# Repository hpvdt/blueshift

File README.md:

# Blueshift

Repository for our what would have been our 2020 ASME entry, Blueshift. Although the vehicle was never completed, the electronics were. The system is heavily based off of TITAN given they are both depend on a video system for the riders which is overlaid with vehicle data.

## Changes from TITAN

 However it has some changes from TITAN:
- Lighting hardware (and control) to meet road legality requirements
- Hardware was designed as an RPi HAT for a more compact system.
- Telemetry was operated by the microcontroller, not the RPi as on TITAN.
- Moved from a Python based overlay system to C based one to improve overlay update rate and prevent the overlay blacking out the video on occasion.

All systems were tested from home during the first set of lockdowns during COVID and were successful. So it is likely they would have worked just as well had the bike been built.

## Outcome

Work on this project ceased once the C-based overlay was working and telemetry was worked into it. Much of what was done for Blueshift will now go into improving TITAN for the future.

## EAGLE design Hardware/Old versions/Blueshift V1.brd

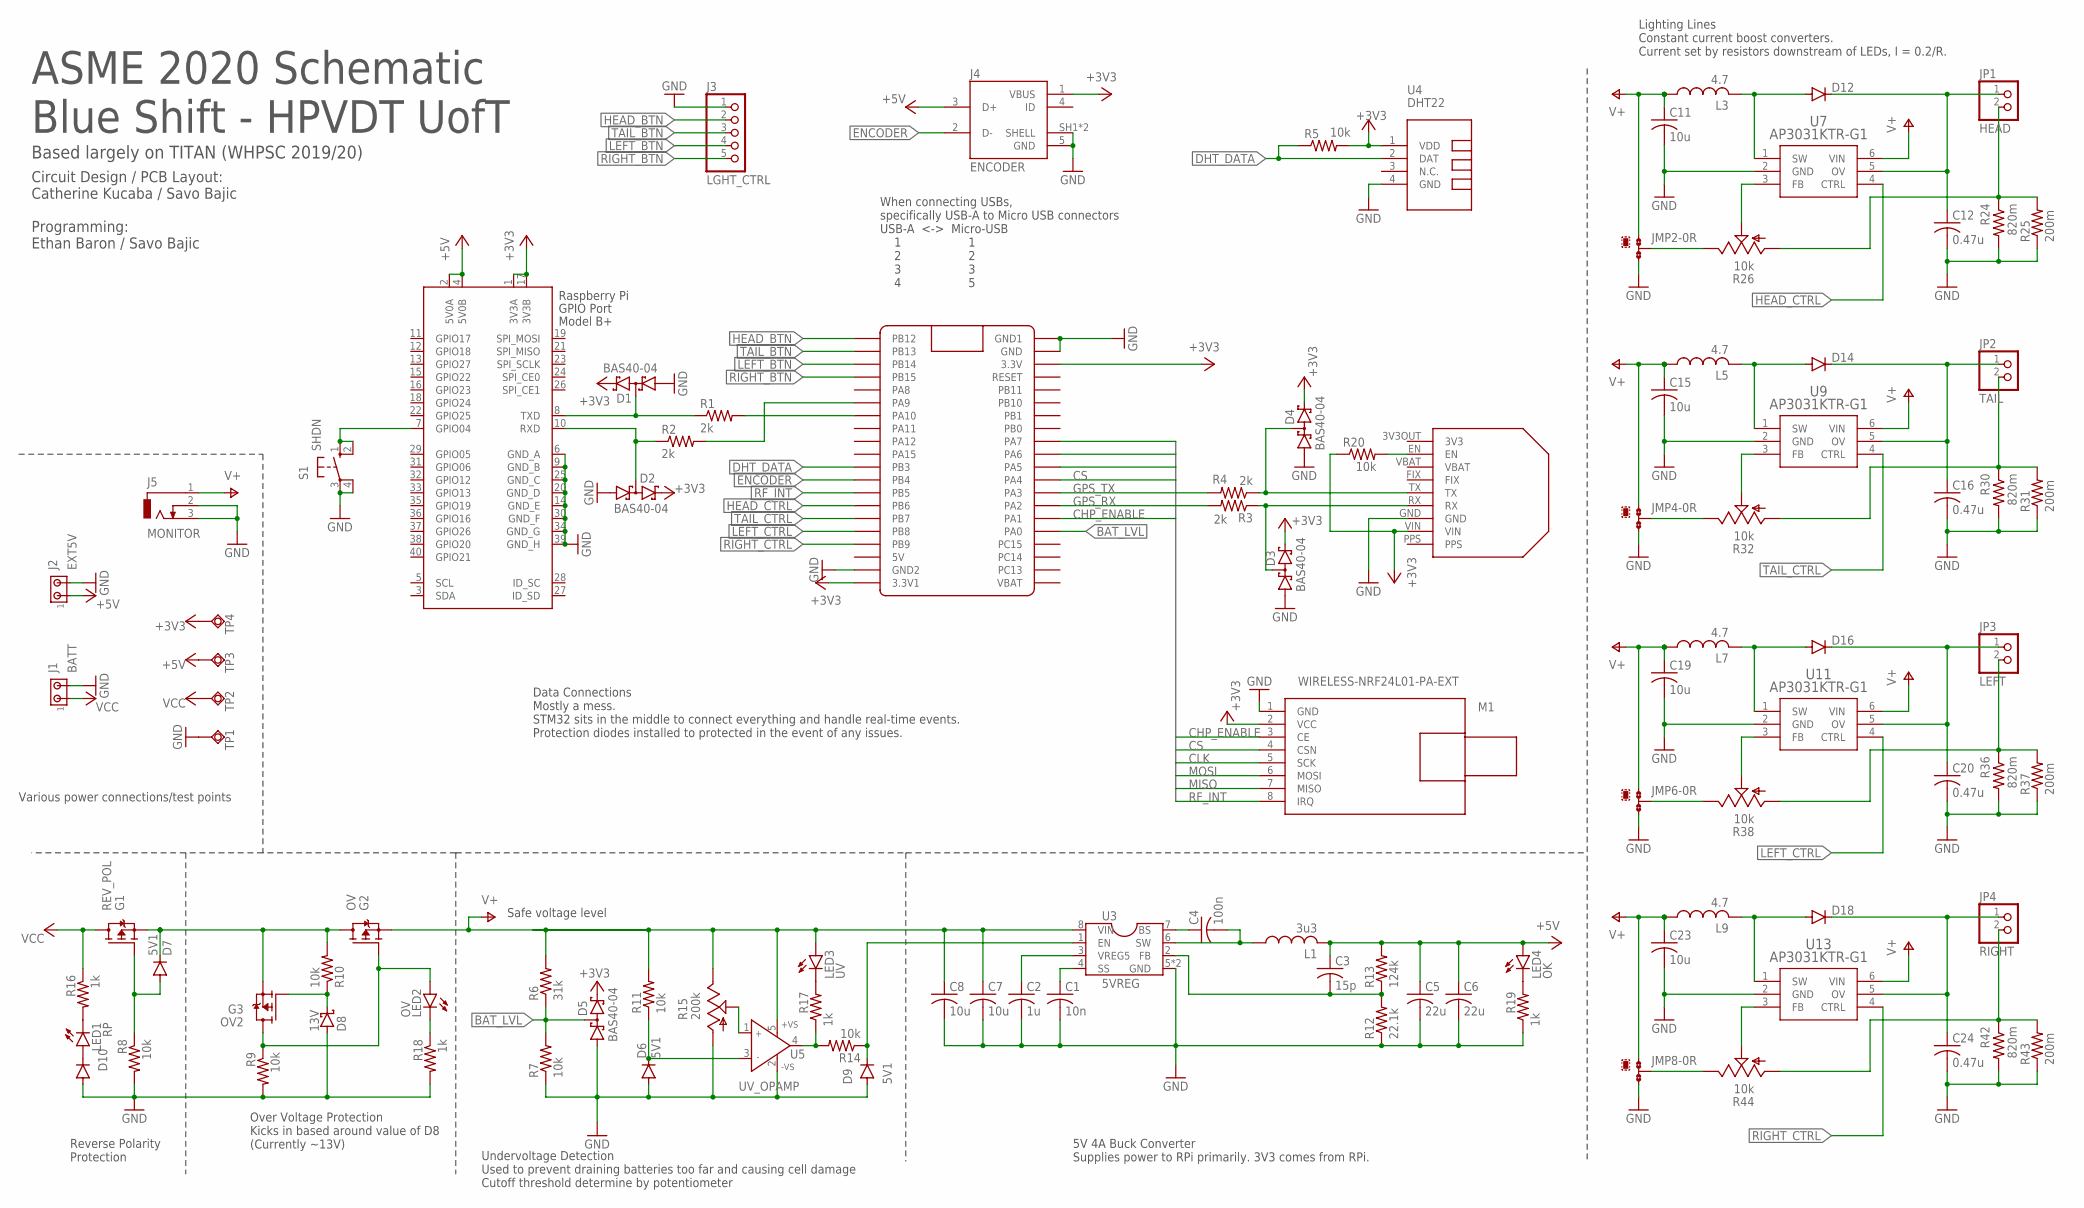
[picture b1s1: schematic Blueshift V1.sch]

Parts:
C1: 10n; C0402
C2: 1u; C0402
C3: 15p; C0402
C4: 100n; C0402
C5, C6: 22u; C0805
C7, C8: 10u; C0805
C11, C15, C19, C23: 10u; C1206K
C12, C16, C20, C24: 0.47u; C1206K
D1, D2, D3, D4, D5: BAS40-04; SOT23
D6, D7, D9: 5V1; SOD323-R
D8: 13V; SOT23
D10: DIODE-SOD80C; SOD80C
D12, D14, D16, D18: DIODE-DO-214AC; DO-214AC
G1: REV_POL; TSOP-6
G2: OV; TSOP-6
G3: OV2; TSOP-6
J1: BATT; 1X2MTA
J2: EXT5V; 1X2MTA
J3: LGHT_CTRL; 1X05
J4: ENCODER; TE_2172034-1
J5: MONITOR; DCJ0303
JMP2, JMP4, JMP6, JMP8: 0R-JUMPA; A0R-JMP
JP1: HEAD; 1X02
JP2: TAIL; 1X02
JP3: LEFT; 1X02
JP4: RIGHT; 1X02
L1: 3u3; SDES064T
L3, L5, L7, L9: 4.7; INDDFN600X600X280-2N
LED1: RP; SML0805
LED2: OV; SML0805
LED3: UV; SML0805
LED4: OK; SML0805
M1: WIRELESS-NRF24L01-PA-EXT
M2: ULTIMATE-GPS; ULTIMATE_GPS
R1, R2, R3, R4: 2k; R0402
R5, R7, R8, R9, R10, R11, R14, R20: 10k; R0402
R6: 31k; R0402
R12: 22.1k; R0402
R13: 124k; R0402
R15: 200k; CA6V
R16, R17, R18, R19: 1k; R0402
R24, R30, R36, R42: 820m; R0603
R25, R31, R37, R43: 200m; R0805
R26, R32, R38, R44: 10k; RJ9W
S1: SHDN; B3F-10XX
TP1: TPSQTP20SQ; TP20SQ
TP2, TP3, TP4: TPSQTP20R; TP20R
U1: RASPI_HAT; RASPI_BOARD_B+HAT_CF
U2: BLUEPILL; BLUE_PILL
U3: 5VREG; SO-8EP
U4: DHT22; TEMP-HUM-SENSOR-DHT22
U5: UV_OPAMP; SOT-753
U7, U9, U11, U13: AP3031KTR-G1; SOT23-6

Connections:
5V_FB: C3.2, R12.2, R13.1, U3.2 (FB)
+3V3: D1.2 (C2), D2.2 (C2), D3.2 (C2), D4.2 (C2), D5.2 (C2), J4.1 (VBUS), M1.2 (VCC), M2.VIN, R5.2, R20.1, TP4.TP, U1.1 (3V3A), U1.17 (3V3B), U2.P$20 (3.3V1), U2.P$23 (3.3V), U4.1 (VDD)
+5V: C3.1, C5.1, C6.1, J2.1, J4.3 (D+), L1.2, LED4.A, R13.2, TP3.TP, U1.2 (5V0A), U1.4 (5V0B)
BAT_LVL: D5.3 (C1A2), R6.1, R7.2, U2.P$36 (PA0)
CHP_ENABLE: M1.3 (CE), U2.P$35 (PA1)
CLK: M1.5 (SCK), U2.P$31 (PA5)
CS: M1.4 (CSN), U2.P$32 (PA4)
DHT_DATA: R5.1, U2.P$11 (PB3), U4.2 (DAT)
ENCODER: J4.2 (D-), U2.P$12 (PB4)
GND: C1.2, C2.2, C5.2, C6.2, C7.2, C8.2, C11.2, C12.2, C15.2, C16.2, C19.2, C20.2, C23.2, C24.2, D1.1 (A1), D2.1 (A1), D3.1 (A1), D4.1 (A1), D5.1 (A1), D6.A, D8.1 (A), D9.A, D10.A, J1.2, J2.2, J3.1, J4.5 (GND), J4.SH1 (SHELL), J4.SH2 (SHELL), J5.2, J5.3, JMP2.3, JMP4.3, JMP6.3, JMP8.3, M1.1 (GND), M2.GND, R7.1, R8.2, R9.2, R12.1, R15.A, R18.2, R19.1, R24.2, R25.1, R30.2, R31.1, R36.2, R37.1, R42.2, R43.1, S1.3, S1.4 (P1), TP1.TP, U1.6 (GND_A), U1.9 (GND_B), U1.14 (GND_E), U1.20 (GND_D), U1.25 (GND_C), U1.30 (GND_F), U1.34 (GND_G), U1.39 (GND_H), U2.P$19 (GND2), U2.P$21 (GND1), U2.P$22 (GND), U3.5 (GND), U3.TP (GND), U4.4 (GND), U5.2 (-VS), U7.2 (GND), U9.2 (GND), U11.2 (GND), U13.2 (GND)
GPS_RX: R3.2, U2.P$34 (PA2)
GPS_TX: R4.2, U2.P$33 (PA3)
HEAD_BTN: J3.2, U2.P$1 (PB12)
HEAD_CTRL: U2.P$14 (PB6), U7.4 (CTRL)
LEFT_BTN: J3.4, U2.P$3 (PB14)
LEFT_CTRL: U2.P$16 (PB8), U11.4 (CTRL)
MISO: M1.7 (MISO), U2.P$30 (PA6)
MOSI: M1.6 (MOSI), U2.P$29 (PA7)
unnamed: R1.2, U2.P$7 (PA10)
unnamed: R2.2, U2.P$6 (PA9)
unnamed: D1.3 (C1A2), R1.1, U1.8 (TXD)
unnamed: D2.3 (C1A2), R2.1, U1.10 (RXD)
unnamed: D3.3 (C1A2), M2.RX, R3.1
unnamed: S1.1 (S), S1.2 (S1), U1.7 (GPIO04)
unnamed: D8.3 (C), G3.3 (G), R10.1
unnamed: D7.A, G1.3 (G), R8.1
unnamed: D4.3 (C1A2), M2.TX, R4.1
unnamed: G2.3 (G), G3.1 (D), G3.2 (D), G3.5 (D), G3.6 (D), LED2.A, R9.1
unnamed: LED3.C, R17.2
unnamed: C1.1, U3.4 (SS)
unnamed: D6.C, R11.1, U5.3 (IN-)
unnamed: C4.2, L1.1, U3.6 (SW)
unnamed: C2.1, U3.3 (VREG5)
unnamed: C4.1, U3.7 (BS)
unnamed: R14.2, R17.1, U5.4 (OUT)
unnamed: D9.C, R14.1, U3.1 (EN)
unnamed: R15.S, U5.1 (IN+)
unnamed: LED1.C, R16.2
unnamed: D10.C, LED1.A
unnamed: M2.EN, R20.2
unnamed: LED2.C, R18.1
unnamed: LED4.C, R19.2
unnamed: D7.C, G1.4 (S), G2.1 (D), G2.2 (D), G2.5 (D), G2.6 (D), G3.4 (S), R10.2
unnamed: D12.A, L3.2, U7.1 (SW)
unnamed: JMP2.2, R26.E
unnamed: R26.S, U7.3 (FB)
unnamed: C12.1, D12.C, JP1.1, U7.5 (OV)
unnamed: JP1.2, R24.1, R25.2, R26.A
unnamed: D14.A, L5.2, U9.1 (SW)
unnamed: JMP4.2, R32.E
unnamed: R32.S, U9.3 (FB)
unnamed: C16.1, D14.C, JP2.1, U9.5 (OV)
unnamed: JP2.2, R30.1, R31.2, R32.A
unnamed: D16.A, L7.2, U11.1 (SW)
unnamed: JMP6.2, R38.E
unnamed: R38.S, U11.3 (FB)
unnamed: C20.1, D16.C, JP3.1, U11.5 (OV)
unnamed: JP3.2, R36.1, R37.2, R38.A
unnamed: D18.A, L9.2, U13.1 (SW)
unnamed: JMP8.2, R44.E
unnamed: R44.S, U13.3 (FB)
unnamed: C24.1, D18.C, JP4.1, U13.5 (OV)
unnamed: JP4.2, R42.1, R43.2, R44.A
RF_INT: M1.8 (IRQ), U2.P$13 (PB5)
RIGHT_BTN: J3.5, U2.P$4 (PB15)
RIGHT_CTRL: U2.P$17 (PB9), U13.4 (CTRL)
TAIL_BTN: J3.3, U2.P$2 (PB13)
TAIL_CTRL: U2.P$15 (PB7), U9.4 (CTRL)
V+: C7.1, C8.1, C11.1, C15.1, C19.1, C23.1, G2.4 (S), J5.1, JMP2.1, JMP4.1, JMP6.1, JMP8.1, L3.1, L5.1, L7.1, L9.1, LED3.A, R6.2, R11.2, R15.E, U3.8 (VIN), U5.5 (+VS), U7.6 (VIN), U9.6 (VIN), U11.6 (VIN), U13.6 (VIN)
VCC: G1.1 (D), G1.2 (D), G1.5 (D), G1.6 (D), J1.1, R16.1, TP2.TP

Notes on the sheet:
When connecting USBs, specifically USB-A to Micro USB connectors USB-A <-> Micro-USB 1 1 2 2 3 3 4 5
Safe voltage level
Various power connections/test points
Undervoltage Detection Used to prevent draining batteries too far and causing cell damage Cutoff threshold determine by potentiometer
5V 4A Buck Converter Supplies power to RPi primarily. 3V3 comes from RPi.
Lighting Lines Constant current boost converters. Current set by resistors downstream of LEDs, I = 0.2/R.
Data Connections Mostly a mess. STM32 sits in the middle to connect everything and handle real-time events. Protection diodes installed to protected in the event of any issues.
Reverse Polarity Protection
Over Voltage Protection Kicks in based around value of D8 (Currently ~13V)
ASME 2020 Schematic Blue Shift - HPVDT UofT
Based largely on TITAN (WHPSC 2019/20)
Circuit Design / PCB Layout: Catherine Kucaba / Savo Bajic Programming: Ethan Baron / Savo Bajic

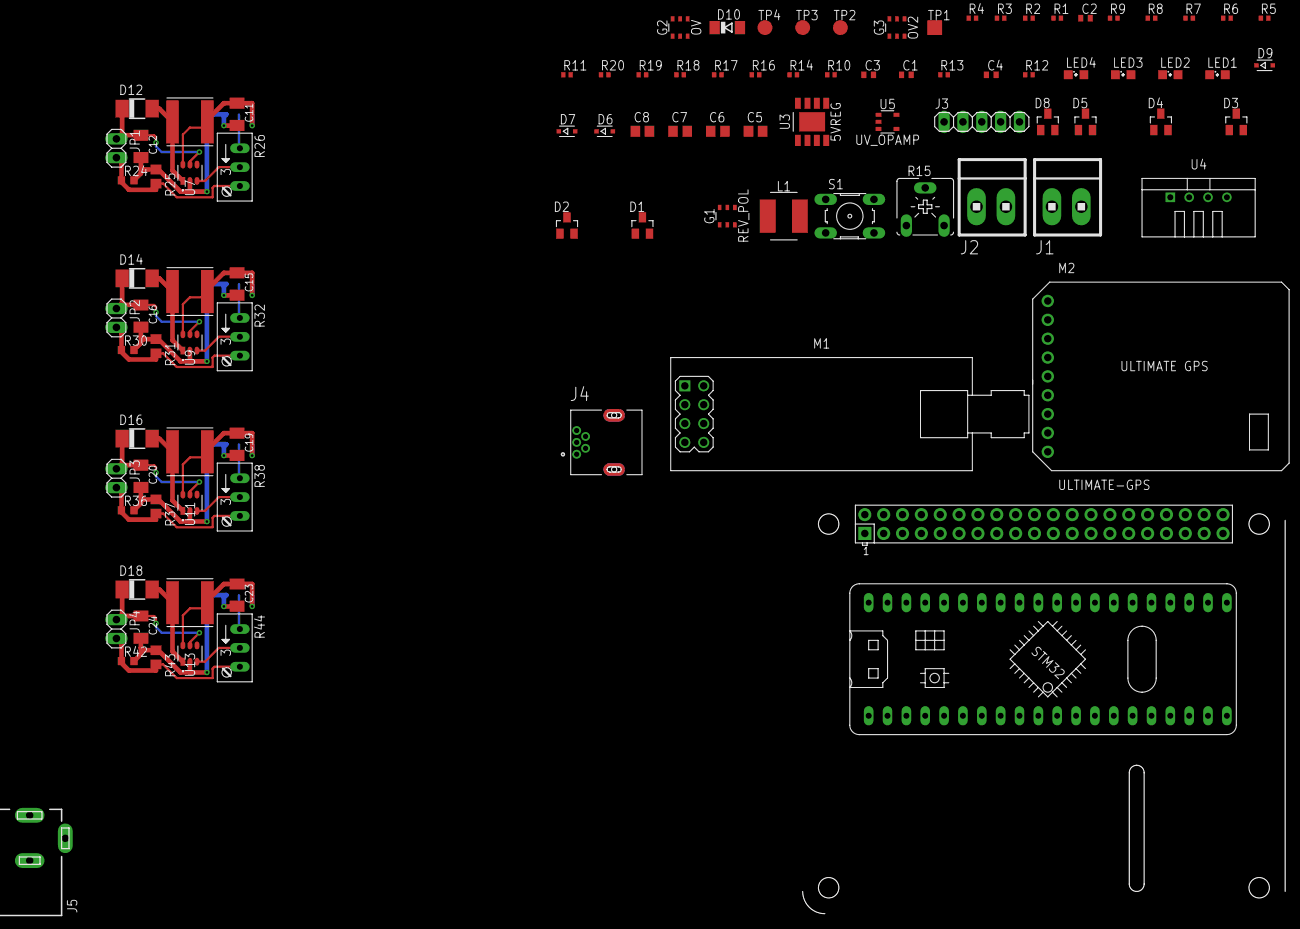
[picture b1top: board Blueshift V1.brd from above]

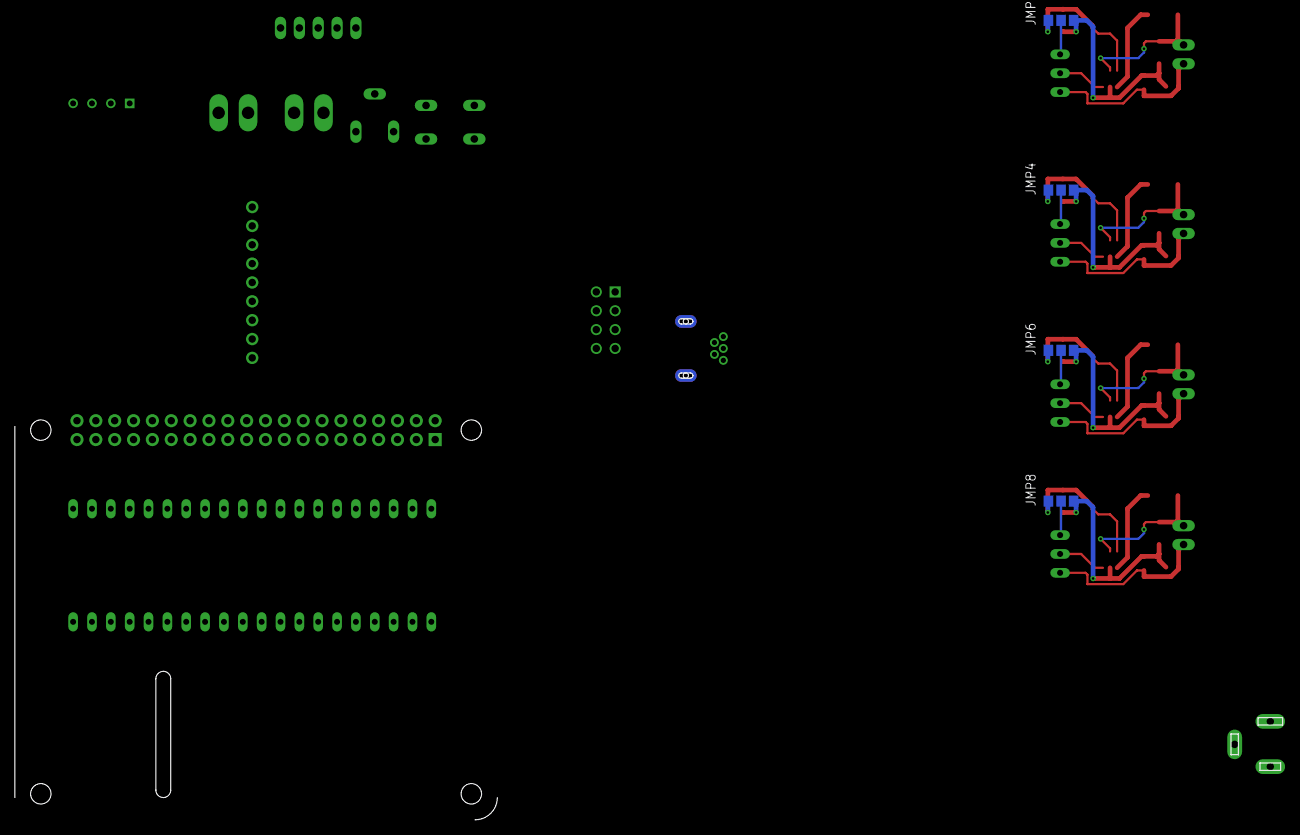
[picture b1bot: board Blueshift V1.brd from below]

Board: 2 copper layers, 103 parts (4 on the bottom side), 70 nets.

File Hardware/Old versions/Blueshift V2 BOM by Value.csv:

"Qty";"Value";"Device";"Package";"Parts";"Description";"";
"4";"";"DIODE-DO-214AC";"DO-214AC";"D12, D14, D16, D18";"DIODE";"";
"1";"";"DIODE-SOD80C";"SOD80C";"D10";"DIODE";"";
"4";"0.47u";"C-USC1206K";"C1206K";"C12, C16, C20, C24";"CAPACITOR, American symbol";"";
"4";"0R-JUMPA";"0R-JUMPA";"A0R-JMP";"JMP2, JMP4, JMP6, JMP8";"SMD 0R 0805 Jumper";"";
"1";"100n";"C-USC0402";"C0402";"C4";"CAPACITOR, American symbol";"";
"12";"10k";"R-US_R0402";"R0402";"R5, R7, R8, R9, R10, R11, R14, R20, R21, R22, R23, R27";"RESISTOR, American symbol";"";
"5";"10k";"TRIM_US-RJ9W";"RJ9W";"R26, R28, R32, R38, R44";"POTENTIOMETER";"";
"1";"10n";"C-USC0402";"C0402";"C1";"CAPACITOR, American symbol";"";
"2";"10u";"C-USC0805";"C0805";"C7, C8";"CAPACITOR, American symbol";"";
"4";"10u";"C-USC1206K";"C1206K";"C11, C15, C19, C23";"CAPACITOR, American symbol";"";
"1";"124k";"R-US_R0402";"R0402";"R13";"RESISTOR, American symbol";"";
"1";"13V";"BAS70";"SOT23";"D8";"Silicon Schottky Diodes";"";
"1";"15p";"C-USC0402";"C0402";"C3";"CAPACITOR, American symbol";"";
"4";"1k";"R-US_R0402";"R0402";"R16, R17, R18, R19";"RESISTOR, American symbol";"";
"1";"1u";"C-USC0402";"C0402";"C2";"CAPACITOR, American symbol";"";
"4";"200m";"R-US_R0805";"R0805";"R25, R31, R37, R43";"RESISTOR, American symbol";"";
"1";"22.1k";"R-US_R0402";"R0402";"R12";"RESISTOR, American symbol";"";
"2";"22u";"C-USC0805";"C0805";"C5, C6";"CAPACITOR, American symbol";"";
"4";"2k";"R-US_R0402";"R0402";"R1, R2, R3, R4";"RESISTOR, American symbol";"";
"1";"31k";"R-US_R0402";"R0402";"R6";"RESISTOR, American symbol";"";
"1";"3u3";"SDES064T-3R3MS";"SDES064T";"L1";"";"";
"4";"4u7";"NR6028NR6028";"INDDFN600X600X280-2N";"L3, L5, L7, L9";"";"";
"3";"5V1";"DIODE-SOD323-R";"SOD323-R";"D6, D7, D9";"DIODE";"";
"1";"5VREG";"AP65450SP-13";"SO-8EP";"U3";"AP65450";"";
"4";"820m";"R-US_R0603";"R0603";"R24, R30, R36, R42";"RESISTOR, American symbol";"";
"4";"AP3031KTR-G1";"AP3031KTR-G1";"SOT23-6";"U7, U9, U11, U13";"AP3031 step-up LED driver chip for LEDs up to 1.4A";"";
"5";"BAS40-04";"BAS40-04";"SOT23";"D1, D2, D3, D4, D5";"Silicon Schottky Diodes";"";
"1";"BATT";"MTA02-156";"1X2MTA";"J1";"AMP connector";"";
"1";"BLUEPILL";"BLUE_PILL";"BLUE_PILL";"U2";"";"";
"1";"DHT22";"TEMP-HUM-SENSOR-DHT22";"TEMP-HUM-SENSOR-DHT22";"U4";"DHT22 - digital humidity & temperature sensor";"";
"1";"ENCODER";"2172034-1";"TE_2172034-1";"J4";"CONN RCPT USB MINI B 2.0 PCB R/A";"";
"1";"EXT5V";"MTA02-156";"1X2MTA";"J2";"AMP connector";"";
"1";"HEAD";"PINHD-1X2";"1X02";"JP1";"PIN HEADER";"";
"1";"LEFT";"PINHD-1X2";"1X02";"JP3";"PIN HEADER";"";
"1";"LGHT_CTRL";"PINHD-1X5";"1X05";"J3";"PIN HEADER";"";
"1";"MONITOR";"DCJ0303";"DCJ0303";"J5";"DC POWER JACK";"";
"1";"OK";"LEDSML0805";"SML0805";"LED4";"LED";"";
"1";"OV";"LEDSML0805";"SML0805";"LED2";"LED";"";
"1";"OV";"SI3493DDV-T1-GE3";"TSOP-6";"G2";"20V P-CH MOSFET";"";
"1";"OV2";"SI3493DDV-T1-GE3";"TSOP-6";"G3";"20V P-CH MOSFET";"";
"1";"RASPI_HAT";"RASPI_HAT";"RASPI_BOARD_B+HAT_CF";"U1";"";"";
"1";"REV_POL";"SI3493DDV-T1-GE3";"TSOP-6";"G1";"20V P-CH MOSFET";"";
"1";"RIGHT";"PINHD-1X2";"1X02";"JP4";"PIN HEADER";"";
"1";"RP";"LEDSML0805";"SML0805";"LED1";"LED";"";
"1";"SHDN";"10-XX";"B3F-10XX";"S1";"OMRON SWITCH";"";
"1";"TAIL";"PINHD-1X2";"1X02";"JP2";"PIN HEADER";"";
"3";"TPSQTP20R";"TPSQTP20R";"TP20R";"TP2, TP3, TP4";"Test pad";"";
"1";"TPSQTP20SQ";"TPSQTP20SQ";"TP20SQ";"TP1";"Test pad";"";
"1";"ULTIMATE-GPS";"ULTIMATE-GPS";"ULTIMATE_GPS";"M2";"";"";
"1";"UV";"LEDSML0805";"SML0805";"LED3";"LED";"";
"1";"UV_OPAMP";"TA75S558F,LF";"SOT-753";"U5";"";"";
"1";"WIRELESS-NRF24L01-PA-EXT";"WIRELESS-NRF24L01-PA-EXT";"WIRELESS-NRF24L01-PA-EXT";"M1";"2.4 GHz Wireless Module based on NRF24L01 chip with preamplifier and external antenna";"";

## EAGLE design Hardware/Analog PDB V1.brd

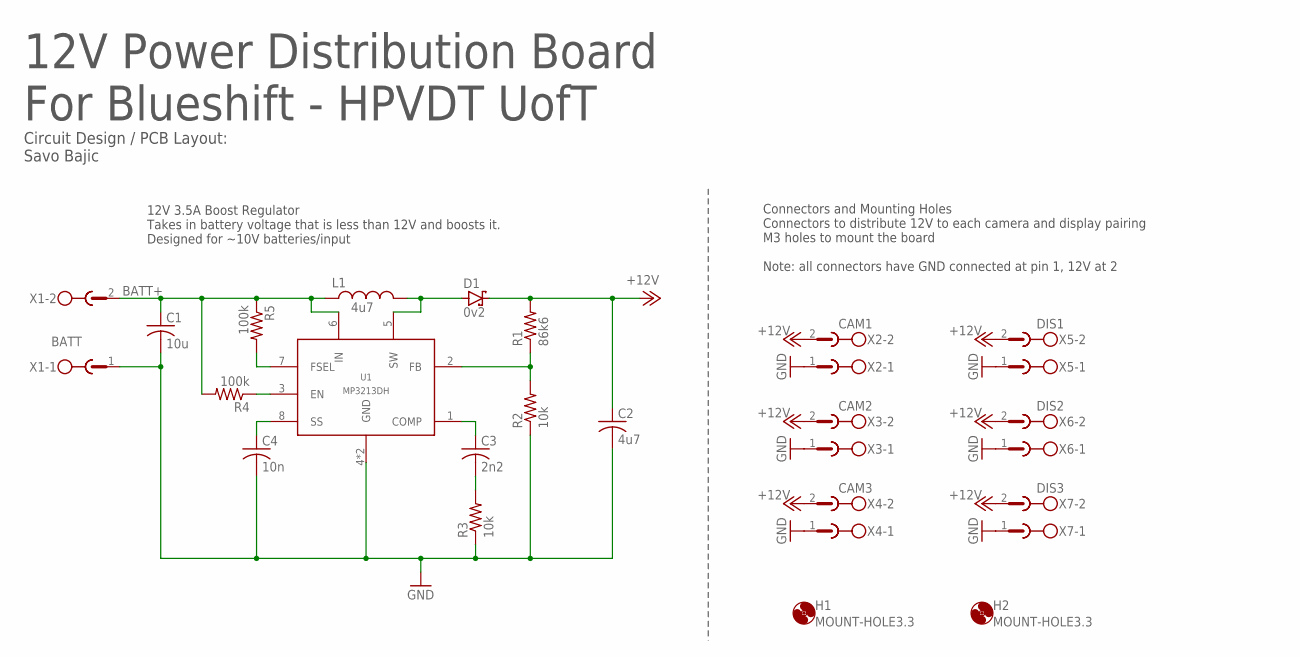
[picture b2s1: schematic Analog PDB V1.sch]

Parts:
C1: 10u; C0603
C2: 4u7; C0603
C3: 2n2; C0603
C4: 10n; C0603
D1: 0v2; DO-214AB
H1, H2: MOUNT-HOLE3.3; 3,3
L1: 4u7; SDES053T
R1: 86k6; R0402
R2, R3: 10k; R0402
R4, R5: 100k; R0402
U1: MP3213DH; 8-TSSOP
X1: BATT; MSTBV2
X2: CAM1; MSTBV2
X3: CAM2; MSTBV2
X4: CAM3; MSTBV2
X5: DIS1; MSTBV2
X6: DIS2; MSTBV2
X7: DIS3; MSTBV2

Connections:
+12V: C2.1, D1.C, R1.2, X2.2, X3.2, X4.2, X5.2, X6.2, X7.2
BATT+: C1.1, L1.1, R4.2, R5.1, U1.6 (IN), X1.2
EN: R4.1, U1.3 (EN)
FEEDBACK: R1.1, R2.2, U1.2 (FB)
FREQSELECT: R5.2, U1.7 (FSEL)
GND: C1.2, C2.2, C4.2, R2.1, R3.1, U1.4 (GND), U1.P (GND), X1.1, X2.1, X3.1, X4.1, X5.1, X6.1, X7.1
unnamed: D1.A, L1.2, U1.5 (SW)
unnamed: C3.1, U1.1 (COMP)
unnamed: C3.2, R3.2
SOFTSTART: C4.1, U1.8 (SS)

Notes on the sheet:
12V 3.5A Boost Regulator Takes in battery voltage that is less than 12V and boosts it. Designed for ~10V batteries/input
Connectors and Mounting Holes Connectors to distribute 12V to each camera and display pairing M3 holes to mount the board Note: all connectors have GND connected at pin 1, 12V at 2
12V Power Distribution Board For Blueshift - HPVDT UofT
Circuit Design / PCB Layout: Savo Bajic

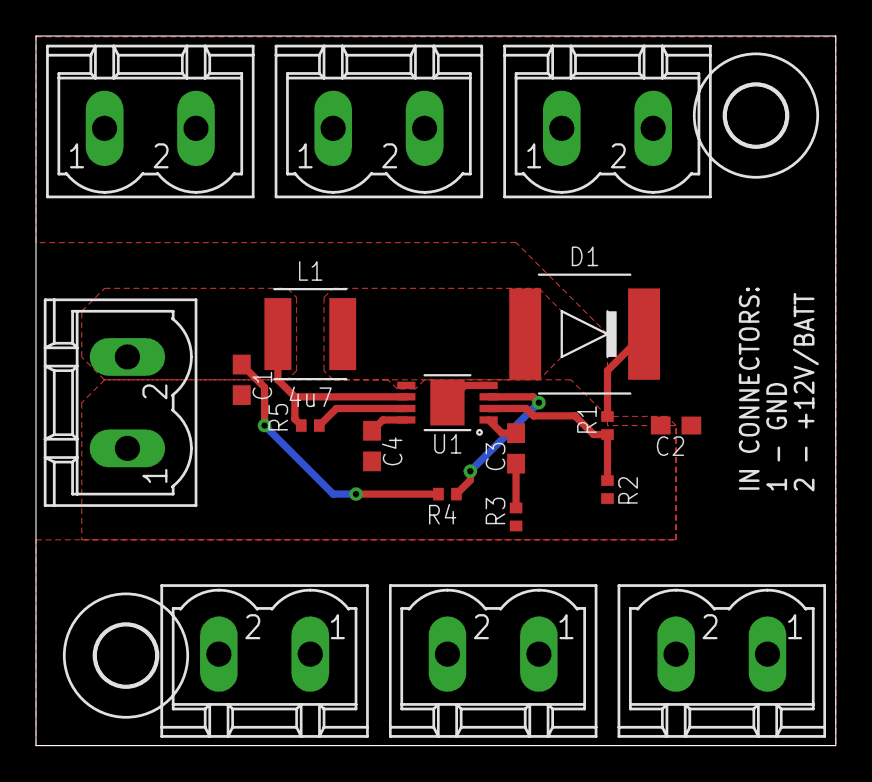
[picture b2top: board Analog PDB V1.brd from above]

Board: 2 copper layers, 44.4 x 39.4 mm, 21 parts (0 on the bottom side), 10 nets.

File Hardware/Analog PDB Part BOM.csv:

"Part";"Value";"Device";"Package";"Description";"";
"C1";"10u";"C-USC0603";"C0603";"CAPACITOR, American symbol";"";
"C2";"4u7";"C-USC0603";"C0603";"CAPACITOR, American symbol";"";
"C3";"2n2";"C-USC0603";"C0603";"CAPACITOR, American symbol";"";
"C4";"10n";"C-USC0603";"C0603";"CAPACITOR, American symbol";"";
"D1";"0v2";"BOOSTDIODE";"DO-214AB";"";"";
"H1";"MOUNT-HOLE3.3";"MOUNT-HOLE3.3";"3,3";"MOUNTING HOLE with drill center marker";"";
"H2";"MOUNT-HOLE3.3";"MOUNT-HOLE3.3";"3,3";"MOUNTING HOLE with drill center marker";"";
"L1";"4u7";"SDEI054T";"SDES053T";"4.7uH Inductor";"";
"R1";"86k6";"R-US_R0402";"R0402";"RESISTOR, American symbol";"";
"R2";"10k";"R-US_R0402";"R0402";"RESISTOR, American symbol";"";
"R3";"10k";"R-US_R0402";"R0402";"RESISTOR, American symbol";"";
"R4";"100k";"R-US_R0402";"R0402";"RESISTOR, American symbol";"";
"R5";"100k";"R-US_R0402";"R0402";"RESISTOR, American symbol";"";
"U1";"MP3213DH";"MP3213DH";"8-TSSOP";"3.5A Boost Converter Regulator";"";
"X1";"BATT";"MST2V";"MSTBV2";"PHOENIX";"";
"X2";"CAM1";"MSTBV2";"MSTBV2";"PHOENIX";"";
"X3";"CAM2";"MSTBV2";"MSTBV2";"PHOENIX";"";
"X4";"CAM3";"MSTBV2";"MSTBV2";"PHOENIX";"";
"X5";"DIS1";"MSTBV2";"MSTBV2";"PHOENIX";"";
"X6";"DIS2";"MSTBV2";"MSTBV2";"PHOENIX";"";
"X7";"DIS3";"MSTBV2";"MSTBV2";"PHOENIX";"";

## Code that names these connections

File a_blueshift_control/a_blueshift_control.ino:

#include <TinyGPS.h>
#include "DHT.h" // Used for temperature and humidity

#define FRONTSERIAL Serial1
#define GPSSERIAL Serial2
#define DEBUGSERIAL Serial
/* Serial Pins
   PA9 - TX1
   PA10 - RX1

   PA2 - TX2
   PA3 - RX2

   PB10 - TX3
   PB11 - RX3
*/

// DEBUGGING MODE
bool debugMode = false;      // In debug mode or not (copies all messages to debug serial line

const long rpiBaud = 115200;  // Baudrate used with rpis
const long gpsBaud = 9600;    // Baudrate used with GPS
const long debugBaud = 115200;  // Baudrate for debugging line

/////////////////////////////////////////////////
// Variables
int FHR = 10;               // Front heart rate (BPM)
int RHR = 10;               // Rear heart rate
int FCadence = 10;          // Cadence (RPM)
int RCadence = 10;
int FPower = 10;            // Power (W)
int RPower = 10;

int FBatt = 100;            // Front battery %
int RBatt = 100;            // Rear battery %
int SBatt = 100;            // Spare battery %

byte humidity = 0;          // Humidity
byte temperature = 50;      // Temperature

volatile float speedKm = 0; // Speed (km/h)
volatile unsigned int rotationCount = 0; // Number of complete wheel roations

float latitude = 0;         // Latitude (degrees)
float longitude = 0;        // Longitude (degrees)
float altitudeGPS = 0;      // Altitude (m)
float speedGPS = 0;         // GPS speed in km/h
float distanceGPS = 0;      // GPS distance in km
// Coordinates that mark the start point (used for getting distance by GPS) 
float startLong = -117.043375;
float startLat = 40.393598;

byte testY = 0;             // Used solely for echo tests
byte testZ = 0;             // Used solely for echo tests

//////////////////////////////////////////////////
// Pin allocation
const byte DHTPin = PB3;  // DHT sensor pin (temperature and humidity)
const byte FBPin = PA0;   // Front battery pin (ADC)
const byte SBPin = PB0;   // Spare battery pin (ADC)
const byte encoderPin = PB4;   // Encoder interrupt pin

// Digital Humidity and Temperature setup
DHT dht(DHTPin, DHT22); // Sets up sensor
const unsigned int dhtPeriod = 500; // Period between measurements
unsigned long dhtTime = 0; // Stores next time to take measurement

// GPS Module
TinyGPS gps;

// Battery monitoring period
const unsigned long batteryPeriod = 2000; // Battery check period (every few seconds)
unsigned long batteryTime = 0;  // Stores time for next battery check

// Wheel monitoring parameters
const byte numberTicks = 6; // Number of ticks per complete rotation of wheel
volatile byte currentTick = 0; // Stores which tick we are on
volatile byte previousTick = numberTicks; // Stores what tick we were previously on

const float periodToKMH = 7495200; // Divide this by period in microseconds to get speed in km/h
// periodToKM is determined by multiplying circumference in meters by 3.6 x 10^6
volatile unsigned long lastPass[numberTicks]; // Stores the last trigger time for each tick
const unsigned long debounce = 4000; // Debounce period in us. Prevents there being repeated measurements from flickering

unsigned long wheelTime = 0; // Check if wheel has timed out (stopped)
const unsigned int wheelTimeout = 500; // Timeout period
float previousSpeed = 0; // Stores speed for comparison

////////////////////////////////////////////////////////////////
// Telemetry related declarations
#include <RF24-STM.h>

const byte radioInteruptPin = PB5;
const byte radioCSPin = PA4;
const byte radioEnablePin = PA1;

// Hardware configuration: Set up nRF24L01 radio on SPI bus plus pins 7 & 8
RF24 radio(radioEnablePin, radioCSPin);
bool recieverRole = true; // Are we the reciever? Vehicle is 'reciever', station is 'sender'

// Communication pipes to use
const uint64_t pipes[2] = { 0x1122334471LL, 0x112233447CLL };

volatile bool recievedRadioData = false; // Used to record a recieve event
char radioMessage[32]; // Buffer for message (nRF24 messages are limited to 32 bytes each)
byte pipeNumber; // Stores the origin of the message (used in reciever mode)









void setup() {
  // Pin modes,
  // !!! verify if encode pin is meant to be pull up or down!!!!!
  pinMode(LED_BUILTIN, OUTPUT); // Used for status indicator
  pinMode(FBPin, INPUT_ANALOG); // Battery pins
  pinMode(SBPin, INPUT_ANALOG);
  pinMode(encoderPin, INPUT_PULLUP); // Encoder interupt

  attachInterrupt(encoderPin, encoderDetect, RISING); // Encoder interupt
  // !!! VERIFY IF FALLING OR RISING !!!

  // Start each serial line
  FRONTSERIAL.begin(rpiBaud);
  GPSSERIAL.begin(gpsBaud);
  DEBUGSERIAL.begin(debugBaud);

  blinker(1500, 5); // Start-up blinking, gives delay for debugging to connect
  
  // Debug timeout
  const int timeout = 2000; // Time out for debugger to be started if debugging
  unsigned long endTime = millis() + timeout; // End time for scanning

  if (debugMode) {
    // Set up debugging mode (USB connection)

    while (!DEBUGSERIAL) {
      delay(100); // wait for serial port to connect. Needed for native USB

      if (millis() > endTime) {
        // Once timeout has been reached
        debugMode = false; // Disable debugging
        break; // Exit loop
      }
    }

    if (debugMode) {
      DEBUGSERIAL.println(F("DEBUGGING MODE")); // Print debug statement if no timeout
      blinker(600, 3);
    }
  }

  // Sensor setup
  dht.begin(); // Starts digital humidity and temperature sensor

  for (byte i = 0; i < numberTicks; i++) {
    lastPass[i] = 0; // Reset all encoder tick values
  }

  setupRadio(); // Set up radio
  
  blinker(100, 10); // Blink a few times on successful startup
}

void loop() {
  if (FRONTSERIAL.available()) {
    // Data on front line
    processData('f');
  }
  if (DEBUGSERIAL.available()) {
    // Data on debugging line
    processData('d');
  }

  // Periodic DHT measurement
  if (millis() > dhtTime) {
    humidity = dht.readHumidity() * 2;            // Humidity reading
    temperature = 50 + (dht.readTemperature() * 2); // Temperature reading

    dhtTime = millis() + dhtPeriod; // Sets next measurement time
  }

  // Periodic battery check
  if (millis() > batteryTime) {
    FBatt = batteryLevel('f');
    SBatt = batteryLevel('s');

    batteryTime = millis() + batteryPeriod; // Sets next check
  }

  // Periodic speed check
  if (millis() > wheelTime) {
    if (speedKm == previousSpeed) speedKm = 0; // Reset speed if no change

    previousSpeed = speedKm; // Updates speed
    wheelTime = millis() + wheelTimeout; // Sets next check
  }

  /////////////////////////////////////////
  // GPS code
  if (GPSSERIAL.available()) {
    GPSCheck();
  }

  //////////////////////////////////////////
  // Telemetry Code
  if (recievedRadioData) {
    recievedRadioData = false; // Clear flag
    radioRecieved();
    processData('t');
  }
  delayMicroseconds(10); // Regular delay
}

void blinker (const int period, const byte repeats) {
  // Blink LED a number of times for a given length
  for (byte i = 0; i < repeats; i++) {
    digitalWrite(LED_BUILTIN, LOW);
    delay(period / 2);
    digitalWrite(LED_BUILTIN, HIGH);
    delay(period / 2);
  }
  // Note on STM32 LED is on when pin is LOW!
}

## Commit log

2020-03-06 Initial commit
    Basically all the TITAN code but with the extra files trimmed out and some renamed to reference Blueshift to avoid confusion
2021-06-07 Uploaded hardware files
2022-03-30 Upload of C based vision tes files
2022-08-08 Changed code to reflect a lack of other boards in Blueshift
2022-08-08 Added found telemetry code

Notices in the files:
parts and their libraries:
diy-modules: Released under the Creative Commons Attribution 4.0 International License: http://creativecommons.org/licenses/by/4.0
